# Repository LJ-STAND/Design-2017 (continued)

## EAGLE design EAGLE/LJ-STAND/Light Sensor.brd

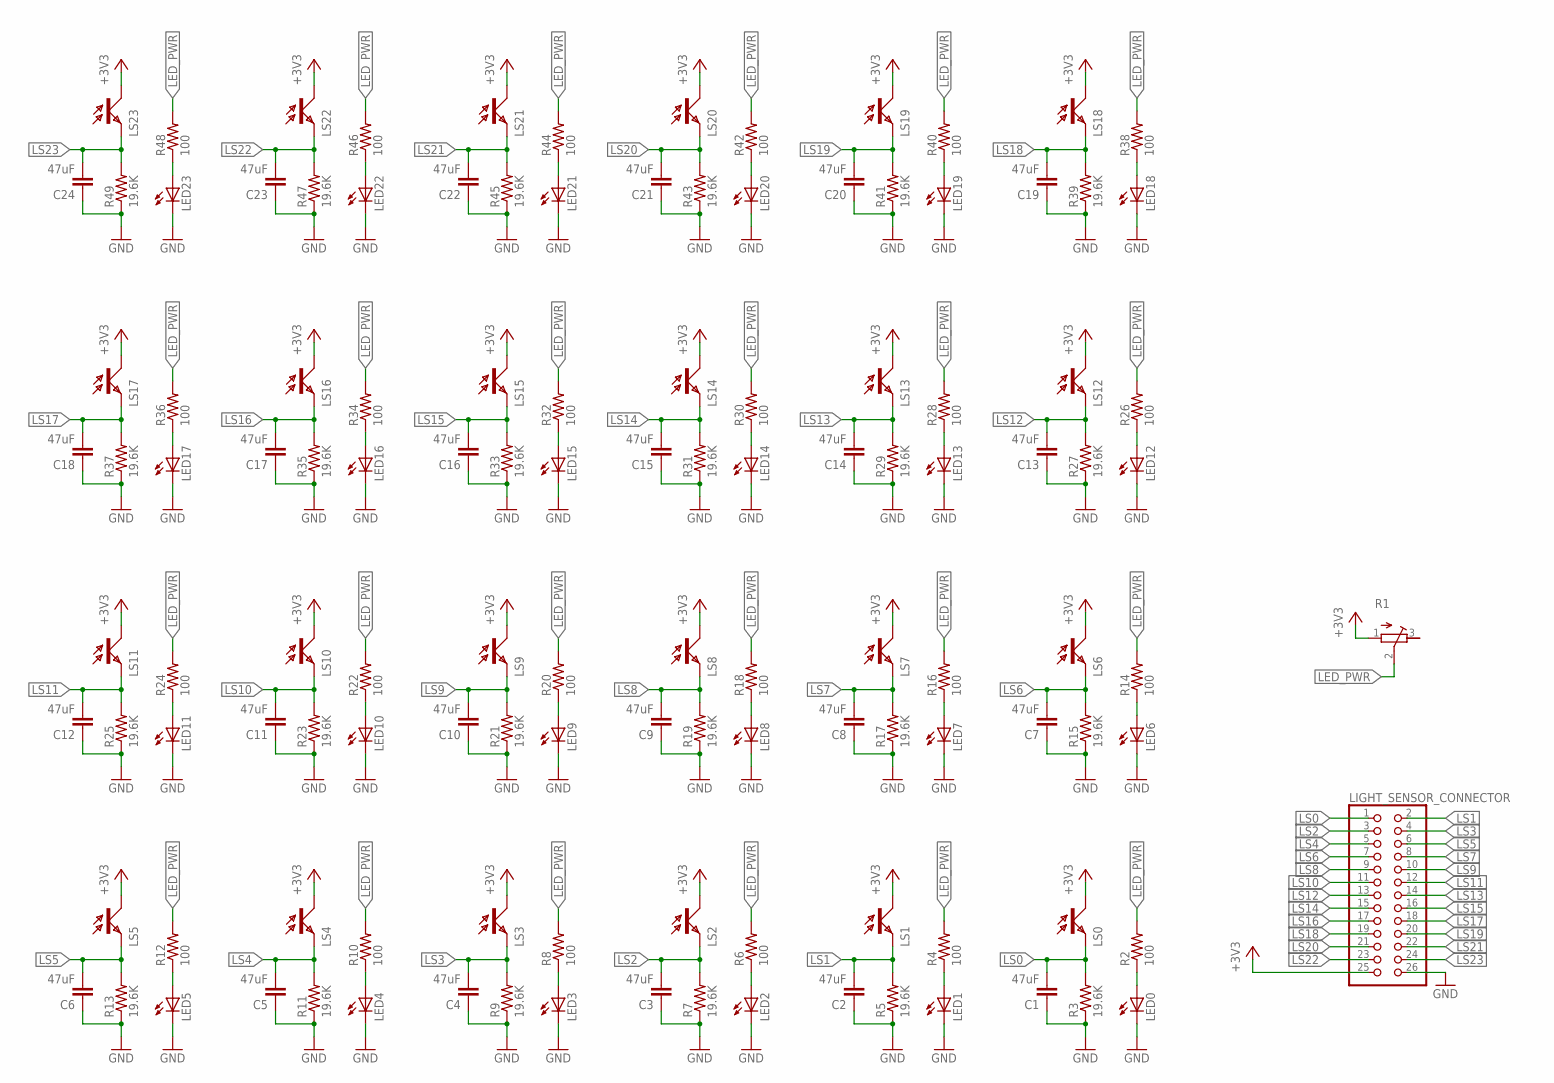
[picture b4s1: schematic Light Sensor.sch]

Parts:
C1, C2, C3, C4, C5, C6, C7, C8, C9, C10, C11, C12, C13, C14, C15, C16, C17, C18, C19, C20, C21, C22, C23, C24: 47uF; 1206
LED0, LED1, LED2, LED3, LED4, LED5, LED6, LED7, LED8, LED9, LED10, LED11, LED12, LED13, LED14, LED15, LED16, LED17, LED18, LED19, LED20, LED21, LED22, LED23: LEDCHIP-LED0603; CHIP-LED0603
LIGHT_SENSOR_CONNECTOR: PINHD-2X13SMT; 2X13_SMT
LS0, LS1, LS2, LS3, LS4, LS5, LS6, LS7, LS8, LS9, LS10, LS11, LS12, LS13, LS14, LS15, LS16, LS17, LS18, LS19, LS20, LS21, LS22, LS23: ALS; SMD
R1: R-TRIMM3296W; RTRIM3296W
R2, R4, R6, R8, R10, R12, R14, R16, R18, R20, R22, R24, R26, R28, R30, R32, R34, R36, R38, R40, R42, R44, R46, R48: 100; 0603-RES
R3, R5, R7, R9, R11, R13, R15, R17, R19, R21, R23, R25, R27, R29, R31, R33, R35, R37, R39, R41, R43, R45, R47, R49: 19.6K; 0603-RES

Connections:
+3V3: LIGHT_SENSOR_CONNECTOR.25, LS0.C, LS1.C, LS2.C, LS3.C, LS4.C, LS5.C, LS6.C, LS7.C, LS8.C, LS9.C, LS10.C, LS11.C, LS12.C, LS13.C, LS14.C, LS15.C, LS16.C, LS17.C, LS18.C, LS19.C, LS20.C, LS21.C, LS22.C, LS23.C, R1.1 (A)
GND: C1.1, C2.1, C3.1, C4.1, C5.1, C6.1, C7.1, C8.1, C9.1, C10.1, C11.1, C12.1, C13.1, C14.1, C15.1, C16.1, C17.1, C18.1, C19.1, C20.1, C21.1, C22.1, C23.1, C24.1, LED0.C, LED1.C, LED2.C, LED3.C, LED4.C, LED5.C, LED6.C, LED7.C, LED8.C, LED9.C, LED10.C, LED11.C, LED12.C, LED13.C, LED14.C, LED15.C, LED16.C, LED17.C, LED18.C, LED19.C, LED20.C, LED21.C, LED22.C, LED23.C, LIGHT_SENSOR_CONNECTOR.26, R3.1, R5.1, R7.1, R9.1, R11.1, R13.1, R15.1, R17.1, R19.1, R21.1, R23.1, R25.1, R27.1, R29.1, R31.1, R33.1, R35.1, R37.1, R39.1, R41.1, R43.1, R45.1, R47.1, R49.1
LED_PWR: R1.2 (S), R2.2, R4.2, R6.2, R8.2, R10.2, R12.2, R14.2, R16.2, R18.2, R20.2, R22.2, R24.2, R26.2, R28.2, R30.2, R32.2, R34.2, R36.2, R38.2, R40.2, R42.2, R44.2, R46.2, R48.2
LS0: C1.2, LIGHT_SENSOR_CONNECTOR.1, LS0.E, R3.2
LS1: C2.2, LIGHT_SENSOR_CONNECTOR.2, LS1.E, R5.2
LS2: C3.2, LIGHT_SENSOR_CONNECTOR.3, LS2.E, R7.2
LS3: C4.2, LIGHT_SENSOR_CONNECTOR.4, LS3.E, R9.2
LS4: C5.2, LIGHT_SENSOR_CONNECTOR.5, LS4.E, R11.2
LS5: C6.2, LIGHT_SENSOR_CONNECTOR.6, LS5.E, R13.2
LS6: C7.2, LIGHT_SENSOR_CONNECTOR.7, LS6.E, R15.2
LS7: C8.2, LIGHT_SENSOR_CONNECTOR.8, LS7.E, R17.2
LS8: C9.2, LIGHT_SENSOR_CONNECTOR.9, LS8.E, R19.2
LS9: C10.2, LIGHT_SENSOR_CONNECTOR.10, LS9.E, R21.2
LS10: C11.2, LIGHT_SENSOR_CONNECTOR.11, LS10.E, R23.2
LS11: C12.2, LIGHT_SENSOR_CONNECTOR.12, LS11.E, R25.2
LS12: C13.2, LIGHT_SENSOR_CONNECTOR.13, LS12.E, R27.2
LS13: C14.2, LIGHT_SENSOR_CONNECTOR.14, LS13.E, R29.2
LS14: C15.2, LIGHT_SENSOR_CONNECTOR.15, LS14.E, R31.2
LS15: C16.2, LIGHT_SENSOR_CONNECTOR.16, LS15.E, R33.2
LS16: C17.2, LIGHT_SENSOR_CONNECTOR.17, LS16.E, R35.2
LS17: C18.2, LIGHT_SENSOR_CONNECTOR.18, LS17.E, R37.2
LS18: C19.2, LIGHT_SENSOR_CONNECTOR.19, LS18.E, R39.2
LS19: C20.2, LIGHT_SENSOR_CONNECTOR.20, LS19.E, R41.2
LS20: C21.2, LIGHT_SENSOR_CONNECTOR.21, LS20.E, R43.2
LS21: C22.2, LIGHT_SENSOR_CONNECTOR.22, LS21.E, R45.2
LS22: C23.2, LIGHT_SENSOR_CONNECTOR.23, LS22.E, R47.2
LS23: C24.2, LIGHT_SENSOR_CONNECTOR.24, LS23.E, R49.2
unnamed: LED0.A, R2.1
unnamed: LED1.A, R4.1
unnamed: LED2.A, R6.1
unnamed: LED3.A, R8.1
unnamed: LED4.A, R10.1
unnamed: LED5.A, R12.1
unnamed: LED6.A, R14.1
unnamed: LED7.A, R16.1
unnamed: LED8.A, R18.1
unnamed: LED9.A, R20.1
unnamed: LED10.A, R22.1
unnamed: LED11.A, R24.1
unnamed: LED12.A, R26.1
unnamed: LED13.A, R28.1
unnamed: LED14.A, R30.1
unnamed: LED15.A, R32.1
unnamed: LED16.A, R34.1
unnamed: LED17.A, R36.1
unnamed: LED18.A, R38.1
unnamed: LED19.A, R40.1
unnamed: LED20.A, R42.1
unnamed: LED21.A, R44.1
unnamed: LED22.A, R46.1
unnamed: LED23.A, R48.1

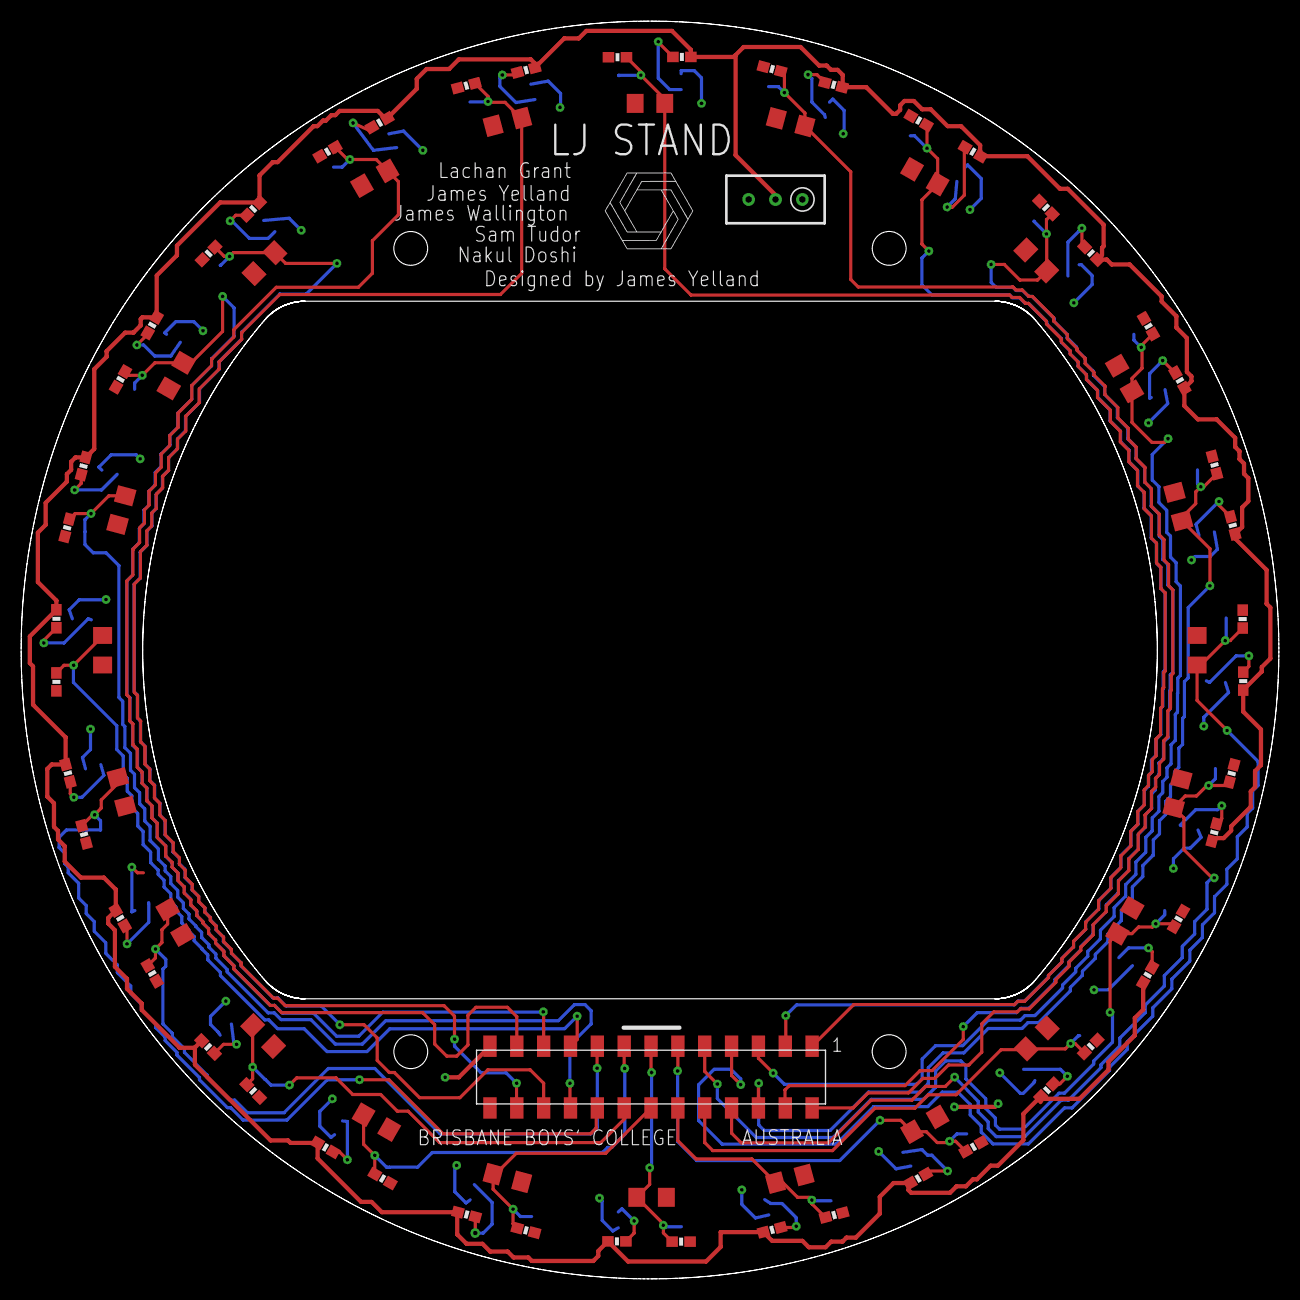
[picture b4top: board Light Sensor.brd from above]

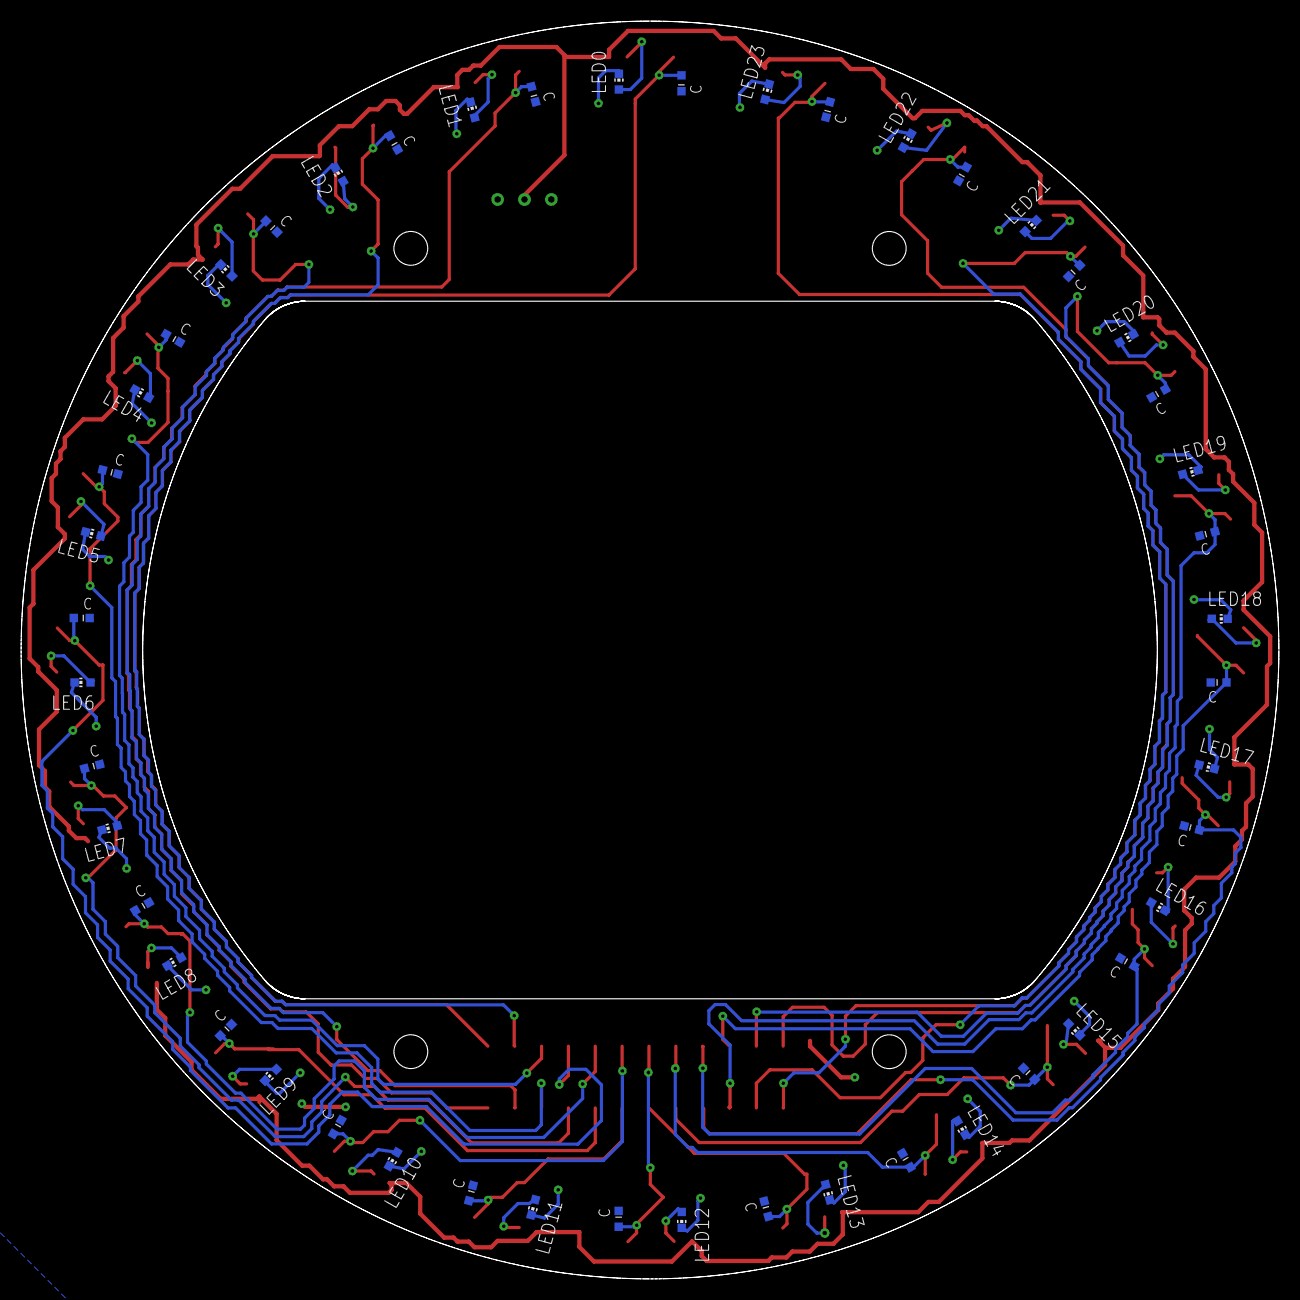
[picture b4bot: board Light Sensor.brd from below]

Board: 2 copper layers, 119.0 x 119.0 mm, 122 parts (48 on the bottom side), 51 nets.

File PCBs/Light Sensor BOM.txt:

Partlist exported from C:/Users/James Yelland/git/LJ-STAND/Design/EAGLE/LJ-STAND/Light Sensor.sch at 30/11/2016 6:50:37 PM

Qty Value Device          Package      Parts                                                                                                                                                        Description    
24        LEDCHIP-LED0805 CHIP-LED0805 LED0, LED1, LED2, LED3, LED4, LED5, LED6, LED7, LED8, LED9, LED10, LED11, LED12, LED13, LED14, LED15, LED16, LED17, LED18, LED19, LED20, LED21, LED22, LED23 LED            
1         PINHD-2X13SMT   2X13_SMT     LIGHT_SENSOR_CONNECTOR                                                                                                                                       PIN HEADER     
1         R-TRIMM3296W    RTRIM3296W   R1                                                                                                                                                           Trimm resistor 
24  100   RESISTOR0603    0603-RES     R2, R4, R6, R8, R10, R12, R14, R16, R18, R20, R22, R24, R26, R28, R30, R32, R34, R36, R38, R40, R42, R44, R46, R48                                           Resistor       
24  19.6K RESISTOR0603    0603-RES     R3, R5, R7, R9, R11, R13, R15, R17, R19, R21, R23, R25, R27, R29, R31, R33, R35, R37, R39, R41, R43, R45, R47, R49                                           Resistor       
24  47uF  CAP1206         1206         C1, C2, C3, C4, C5, C6, C7, C8, C9, C10, C11, C12, C13, C14, C15, C16, C17, C18, C19, C20, C21, C22, C23, C24                                                Capacitor      
24  ALS   ALS             SMD          LS0, LS1, LS2, LS3, LS4, LS5, LS6, LS7, LS8, LS9, LS10, LS11, LS12, LS13, LS14, LS15, LS16, LS17, LS18, LS19, LS20, LS21, LS22, LS23

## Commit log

2016-08-02 Design, has cool middle plate
2016-08-02 Lots of changes
2016-08-02 Inventor saves
2016-08-09 Removed design, started new one
2016-08-09 Bottom & middle plates
2016-08-09 TSOP Ring
2016-08-11 Moved front of robot in
2016-08-15 Ideas text file
2016-08-15 Tings
2016-09-20 Lots of things
2016-09-20 Stuff
2016-09-20 Merge
2016-09-21 More stuffs
2016-09-24 Lots more things, kicker stuff
2016-09-26 Parts list
2016-09-26 EAGLE
2016-09-26 Parts & EAGLE
2016-09-28 Teensy library
2016-09-28 Motor controllers
2016-09-28 Lock fixes
2016-09-28 Pixy
2016-09-29 Things
2016-10-02 Hexagon
2016-10-03 Light sensor PCB
2016-10-10 Stuffs
2016-10-10 Logic level converters
2016-10-10 Clean-up
2016-10-12 Eagle stuffs
2016-10-13 Combined I2C & SPI buses into one of each
2016-10-13 Tsop array
2016-10-13 Light sensor holes
2016-10-14 Top plate
2016-10-14 Ugly switch holes
2016-10-14 TSOPS placed on pcb and lots of other stuff
2016-10-14 PCB Routing
2016-10-15 TSOP wires routed. Sanity gone.
2016-10-15 Finished main PCB routing
2016-10-18 Wheels
2016-10-18 Wheels finished
2016-10-19 Light PCB
2016-10-20 GND plane spacing
2016-10-25 Added some components to light sensor PCB
2016-10-28 Teensys
2016-10-28 Light sensor connector
2016-10-28 Trimpot on light pcb
2016-10-30 Filtering cap on motor controllers
2016-10-30 Diode
2016-10-30 Standoff material
2016-10-31 Motor support
2016-11-01 Front mount
2016-11-02 Schematic things, removed main board file :/
2016-11-03 LDR hole
2016-11-04 5V Diode
2016-11-05 Finished light sensor schematic
2016-11-08 eagle things
2016-11-08 DXFs for PCBs
2016-11-09 Front mount changes
2016-11-09 Renders
2016-11-09 PCB Image
2016-11-10 DXF files
2016-11-10 Change ULP Script
2016-11-10 PDFs
2016-11-10 DXF files - actually this time
2016-11-11 Removed traces, fixed names - light pcb
2016-11-11 Redid dimension
2016-11-11 Some traces on light
2016-11-11 More traces
2016-11-11 finished light sensor pcb
2016-11-11 Light PCB Text
2016-11-11 Rebuilt robot assembly using proper fasteners
2016-11-11 Pixy & switches
2016-11-11 Inventor files
2016-11-12 Logo on light pcb
2016-11-12 main pcb stuff
2016-11-14 Main pcb
2016-11-17 Extended front of top plate
2016-11-22 new top plate
2016-11-24 More main pcb routing
2016-11-24 More routing
2016-11-24 Pcb routing done
2016-11-24 Pin names and drill holes
2016-11-24 PCB design errors
2016-11-24 bigger motor traces
2016-11-25 Light sensor PCB error fixing
2016-11-26 Main pcb check against dimensions, made text bigger on both pcbs
2016-11-26 PCB finalising
2016-11-27 Switches
2016-11-28 Top plate things
2016-11-28 Fasteners
2016-11-29 Sonar Mounts
2016-11-29 Sonars
2016-11-29 Renders & logo
2016-11-29 Silkscreen changes
2016-11-29 Bigger motor mounts
2016-11-30 Pcbs
2016-11-30 PCB checks
2016-11-30 Pcb checking
2016-11-30 Change to 3.3v vreg library
2016-11-30 Fixed 3.3v vreg pins
2016-11-30 1000uf cap move
2016-11-30 more pcb checking
2016-11-30 Plates and 3D print export
2016-11-30 checklist
2016-11-30 Plates
2016-12-01 Design & PCB finalisation
2016-12-01 Pcb stuf
2016-12-03 Finalising
2016-12-03 changed 0805 to 0603 leds
2016-12-03 PCB fixing
2016-12-03 LED Changes
2017-01-31 Larger motor mount holes
2017-01-31 Eagle files
2017-01-31 Bigger LDR Hole
2017-02-03 Lower res bbc logo
2017-02-04 small bbc logo bmp
2017-02-04 Gerbers
2017-03-07 experimenting with motor angles, eagle files
2017-03-07 Updated EAGLE
2017-03-11 Changed Motor Angles
2017-03-12 model and plate exports
2017-03-12 New plate PDFs
2017-03-12 Moved renders to dropbox
2017-03-12 Removed out of date plate PDFs
2017-03-16 Solenoid circuit
2017-03-19 Solenoid circuit - added fet & relay and capacitor
2017-03-21 Kicker pcb sketch
2017-03-21 Hexagon too small
2017-03-21 hex kicker pcb outline - too small
2017-03-23 Kicker pcb - from a few days ago
2017-03-23 Light sensor cover
2017-03-23 Light Sensor Cover laser cutting
2017-03-27 Fixed small tsop hole
2017-03-27 Lowered TSOP ring, dribbler motor block
2017-04-06 Kicker PCB -> Dribbler PCB
2017-05-18 New motor angles, new light gate plates
2017-05-19 XBee mount
2017-05-19 Smaller light gate mount holes, dwg exports of new plates
2017-05-29 Top down render
2017-06-24 Back ball capture zone
2017-06-24 New plate exports
2017-06-24 OBJ file, top down render
2017-06-24 Removed accidental hole in bottom plate
2017-06-24 STL export
2017-06-24 PDF exports
2017-07-08 Top plate fix, ball capture zone light sensor stuff
2017-07-10 Final plate and capture zone cover designs, exports
2017-07-10 Plate PDF's
2017-07-10 AutoCAD save
2017-08-10 Tall handle
2017-08-10 Tall handle pdf
